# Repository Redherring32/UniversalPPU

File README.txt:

Release date: August 11, 2014

Contained within is all the information you should need to build and program your very own Universal PPU.

Here are the brief programming instructions:
1. Load the microcontroller with the firmware.  You will need a Pickit or equivalent programmer to do this.
2. Load PaletteMaker.  Write out a palette file.
3. Connect the Universal PPU to your computer via a USB cable.
4. Load UniversalPpuConfig.  Connect to your Universal PPU.
5. Under the FPGA tab, load universalppu.bin (NOT universalppu.bit).  Write the FPGA.
6. Under the Palette tab, load your palette file.  Write it.

And that's it!  Good luck!

Please note that there is no warranty nor any support offered for the contents of this archive.  
Assembling your own Universal PPU is strictly at your own risk.

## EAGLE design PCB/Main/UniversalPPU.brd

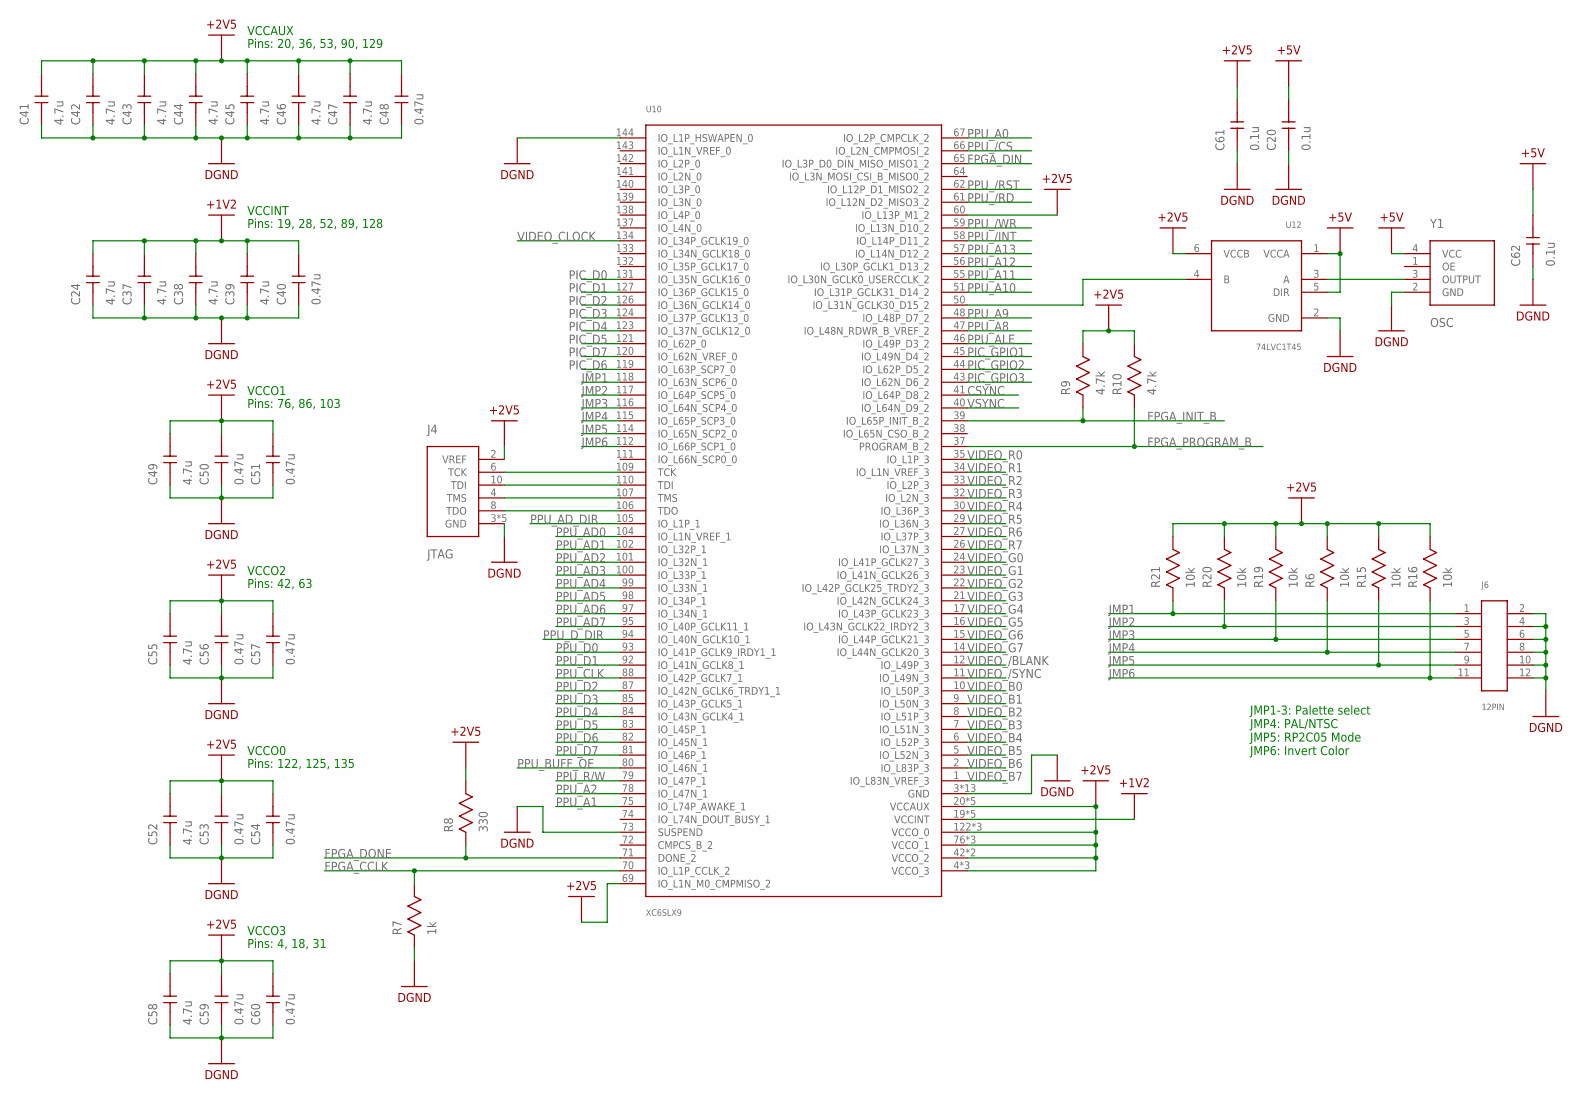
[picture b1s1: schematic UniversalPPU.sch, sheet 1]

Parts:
C20, C61, C62: 0.1u; TDK_C0816
C24, C37, C38, C39, C41, C42, C43, C44, C45, C46, C47, C49, C52, C55, C58: 4.7u; TDK_C0816
C40, C48, C50, C51, C53, C54, C56, C57, C59, C60: 0.47u; TDK_C0816
J4: JTAG; 14PIN_2MM
J6: 12PIN
R6, R15, R16, R19, R20, R21: 10k; 0603
R7: 1k; 0603
R8: 330; 0603
R9, R10: 4.7k; 0603
U10: XC6SLX9; TQG144
U12: 74LVC1T45; R-PDSO-G6
Y1: OSC

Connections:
+1V2: C24.2, C37.2, C38.2, C39.2, C40.2, U10.19 (VCCINT), U10.28 (VCCINT), U10.52 (VCCINT), U10.89 (VCCINT), U10.128 (VCCINT); also elsewhere on the board
+2V5: C41.2, C42.2, C43.2, C44.2, C45.2, C46.2, C47.2, C48.2, C49.2, C50.2, C51.2, C52.2, C53.2, C54.2, C55.2, C56.2, C57.2, C58.2, C59.2, C60.2, C61.2, J4.2 (VREF), R6.P$2, R8.P$2, R9.P$2, R10.P$2, R15.P$2, R16.P$2, R19.P$2, R20.P$2, R21.P$2, U10.4 (VCCO_3), U10.18 (VCCO_3), U10.20 (VCCAUX), U10.31 (VCCO_3), U10.36 (VCCAUX), U10.42 (VCCO_2), U10.53 (VCCAUX), U10.60 (IO_L13P_M1_2), U10.63 (VCCO_2), U10.69 (IO_L1N_M0_CMPMISO_2), U10.76 (VCCO_1), U10.86 (VCCO_1), U10.90 (VCCAUX), U10.103 (VCCO_1), U10.122 (VCCO_0), U10.125 (VCCO_0), U10.129 (VCCAUX), U10.135 (VCCO_0), U12.6 (VCCB); also elsewhere on the board
+5V: C20.2, C62.2, U12.1 (VCCA), U12.5 (DIR), Y1.4 (VCC); also elsewhere on the board
CSYNC: U10.41 (IO_L64P_D8_2); also elsewhere on the board
DGND: C20.1, C24.1, C37.1, C38.1, C39.1, C40.1, C41.1, C42.1, C43.1, C44.1, C45.1, C46.1, C47.1, C48.1, C49.1, C50.1, C51.1, C52.1, C53.1, C54.1, C55.1, C56.1, C57.1, C58.1, C59.1, C60.1, C61.1, C62.1, J4.3 (GND), J4.5 (GND), J4.7 (GND), J4.9 (GND), J4.11 (GND), J6.2, J6.4, J6.6, J6.8, J6.10, J6.12, R7.P$1, U10.3 (GND), U10.13 (GND), U10.25 (GND), U10.49 (GND), U10.54 (GND), U10.68 (GND), U10.73 (SUSPEND), U10.77 (GND), U10.91 (GND), U10.96 (GND), U10.108 (GND), U10.113 (GND), U10.130 (GND), U10.136 (GND), U10.144 (IO_L1P_HSWAPEN_0), U12.2 (GND), Y1.2 (GND); also elsewhere on the board
FPGA_CCLK: R7.P$2, U10.70 (IO_L1P_CCLK_2); also elsewhere on the board
FPGA_DIN: U10.65 (IO_L3P_D0_DIN_MISO_MISO1_2); also elsewhere on the board
FPGA_DONE: R8.P$1, U10.71 (DONE_2); also elsewhere on the board
FPGA_INIT_B: R9.P$1, U10.39 (IO_L65P_INIT_B_2); also elsewhere on the board
FPGA_PROGRAM_B: R10.P$1, U10.37 (PROGRAM_B_2); also elsewhere on the board
JMP1: J6.1, R21.P$1, U10.118 (IO_L63N_SCP6_0)
JMP2: J6.3, R20.P$1, U10.117 (IO_L64P_SCP5_0)
JMP3: J6.5, R19.P$1, U10.116 (IO_L64N_SCP4_0)
JMP4: J6.7, R6.P$1, U10.115 (IO_L65P_SCP3_0)
JMP5: J6.9, R15.P$1, U10.114 (IO_L65N_SCP2_0)
JMP6: J6.11, R16.P$1, U10.112 (IO_L66P_SCP1_0)
unnamed: U10.50 (IO_L31N_GCLK30_D15_2), U12.4 (B)
unnamed: U12.3 (A), Y1.3 (OUTPUT)
PIC_D0: U10.131 (IO_L35N_GCLK16_0); also elsewhere on the board
PIC_D1: U10.127 (IO_L36P_GCLK15_0); also elsewhere on the board
PIC_D2: U10.126 (IO_L36N_GCLK14_0); also elsewhere on the board
PIC_D3: U10.124 (IO_L37P_GCLK13_0); also elsewhere on the board
PIC_D4: U10.123 (IO_L37N_GCLK12_0); also elsewhere on the board
PIC_D5: U10.121 (IO_L62P_0); also elsewhere on the board
PIC_D6: U10.119 (IO_L63P_SCP7_0); also elsewhere on the board
PIC_D7: U10.120 (IO_L62N_VREF_0); also elsewhere on the board
PIC_GPIO1: U10.45 (IO_L49N_D4_2); also elsewhere on the board
PIC_GPIO2: U10.44 (IO_L62P_D5_2); also elsewhere on the board
PIC_GPIO3: U10.43 (IO_L62N_D6_2); also elsewhere on the board
PPU_/CS: U10.66 (IO_L2N_CMPMOSI_2); also elsewhere on the board
PPU_/INT: U10.58 (IO_L14P_D11_2); also elsewhere on the board
PPU_/RD: U10.61 (IO_L12N_D2_MISO3_2); also elsewhere on the board
PPU_/RST: U10.62 (IO_L12P_D1_MISO2_2); also elsewhere on the board
PPU_/WR: U10.59 (IO_L13N_D10_2); also elsewhere on the board
PPU_A0: U10.67 (IO_L2P_CMPCLK_2); also elsewhere on the board
PPU_A1: U10.75 (IO_L74P_AWAKE_1); also elsewhere on the board
PPU_A2: U10.78 (IO_L47N_1); also elsewhere on the board
PPU_A8: U10.47 (IO_L48N_RDWR_B_VREF_2); also elsewhere on the board
PPU_A9: U10.48 (IO_L48P_D7_2); also elsewhere on the board
PPU_A10: U10.51 (IO_L31P_GCLK31_D14_2); also elsewhere on the board
PPU_A11: U10.55 (IO_L30N_GCLK0_USERCCLK_2); also elsewhere on the board
PPU_A12: U10.56 (IO_L30P_GCLK1_D13_2); also elsewhere on the board
PPU_A13: U10.57 (IO_L14N_D12_2); also elsewhere on the board
PPU_AD0: U10.104 (IO_L1N_VREF_1); also elsewhere on the board
PPU_AD1: U10.102 (IO_L32P_1); also elsewhere on the board
PPU_AD2: U10.101 (IO_L32N_1); also elsewhere on the board
PPU_AD3: U10.100 (IO_L33P_1); also elsewhere on the board
PPU_AD4: U10.99 (IO_L33N_1); also elsewhere on the board
PPU_AD5: U10.98 (IO_L34P_1); also elsewhere on the board
PPU_AD6: U10.97 (IO_L34N_1); also elsewhere on the board
PPU_AD7: U10.95 (IO_L40P_GCLK11_1); also elsewhere on the board
PPU_AD_DIR: U10.105 (IO_L1P_1); also elsewhere on the board
PPU_ALE: U10.46 (IO_L49P_D3_2); also elsewhere on the board
PPU_BUFF_OE: U10.80 (IO_L46N_1); also elsewhere on the board
PPU_CLK: U10.88 (IO_L42P_GCLK7_1); also elsewhere on the board
PPU_D0: U10.93 (IO_L41P_GCLK9_IRDY1_1); also elsewhere on the board
PPU_D1: U10.92 (IO_L41N_GCLK8_1); also elsewhere on the board
PPU_D2: U10.87 (IO_L42N_GCLK6_TRDY1_1); also elsewhere on the board
PPU_D3: U10.85 (IO_L43P_GCLK5_1); also elsewhere on the board
PPU_D4: U10.84 (IO_L43N_GCLK4_1); also elsewhere on the board
PPU_D5: U10.83 (IO_L45P_1); also elsewhere on the board
PPU_D6: U10.82 (IO_L45N_1); also elsewhere on the board
PPU_D7: U10.81 (IO_L46P_1); also elsewhere on the board
PPU_D_DIR: U10.94 (IO_L40N_GCLK10_1); also elsewhere on the board
PPU_R/W: U10.79 (IO_L47P_1); also elsewhere on the board
TCK: J4.6 (TCK), U10.109 (TCK)
TDI: J4.10 (TDI), U10.110 (TDI)
TDO: J4.8 (TDO), U10.106 (TDO)
TMS: J4.4 (TMS), U10.107 (TMS)
VIDEO_/BLANK: U10.12 (IO_L49P_3); also elsewhere on the board
VIDEO_/SYNC: U10.11 (IO_L49N_3); also elsewhere on the board
VIDEO_B0: U10.10 (IO_L50P_3); also elsewhere on the board
VIDEO_B1: U10.9 (IO_L50N_3); also elsewhere on the board
VIDEO_B2: U10.8 (IO_L51P_3); also elsewhere on the board
VIDEO_B3: U10.7 (IO_L51N_3); also elsewhere on the board
VIDEO_B4: U10.6 (IO_L52P_3); also elsewhere on the board
VIDEO_B5: U10.5 (IO_L52N_3); also elsewhere on the board
VIDEO_B6: U10.2 (IO_L83P_3); also elsewhere on the board
VIDEO_B7: U10.1 (IO_L83N_VREF_3); also elsewhere on the board
VIDEO_CLOCK: U10.134 (IO_L34P_GCLK19_0); also elsewhere on the board
VIDEO_G0: U10.24 (IO_L41P_GCLK27_3); also elsewhere on the board
VIDEO_G1: U10.23 (IO_L41N_GCLK26_3); also elsewhere on the board
VIDEO_G2: U10.22 (IO_L42P_GCLK25_TRDY2_3); also elsewhere on the board
VIDEO_G3: U10.21 (IO_L42N_GCLK24_3); also elsewhere on the board
VIDEO_G4: U10.17 (IO_L43P_GCLK23_3); also elsewhere on the board
VIDEO_G5: U10.16 (IO_L43N_GCLK22_IRDY2_3); also elsewhere on the board
VIDEO_G6: U10.15 (IO_L44P_GCLK21_3); also elsewhere on the board
VIDEO_G7: U10.14 (IO_L44N_GCLK20_3); also elsewhere on the board
VIDEO_R0: U10.35 (IO_L1P_3); also elsewhere on the board
VIDEO_R1: U10.34 (IO_L1N_VREF_3); also elsewhere on the board
VIDEO_R2: U10.33 (IO_L2P_3); also elsewhere on the board
VIDEO_R3: U10.32 (IO_L2N_3); also elsewhere on the board
VIDEO_R4: U10.30 (IO_L36P_3); also elsewhere on the board
VIDEO_R5: U10.29 (IO_L36N_3); also elsewhere on the board
VIDEO_R6: U10.27 (IO_L37P_3); also elsewhere on the board
VIDEO_R7: U10.26 (IO_L37N_3); also elsewhere on the board
VSYNC: U10.40 (IO_L64N_D9_2); also elsewhere on the board

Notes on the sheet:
VCCINT
VCCAUX
VCCO1
VCCO2
VCCO0
VCCO3
JMP1-3: Palette select JMP4: PAL/NTSC JMP5: RP2C05 Mode JMP6: Invert Color
Pins: 20, 36, 53, 90, 129
Pins: 19, 28, 52, 89, 128
Pins: 76, 86, 103
Pins: 42, 63
Pins: 122, 125, 135
Pins: 4, 18, 31

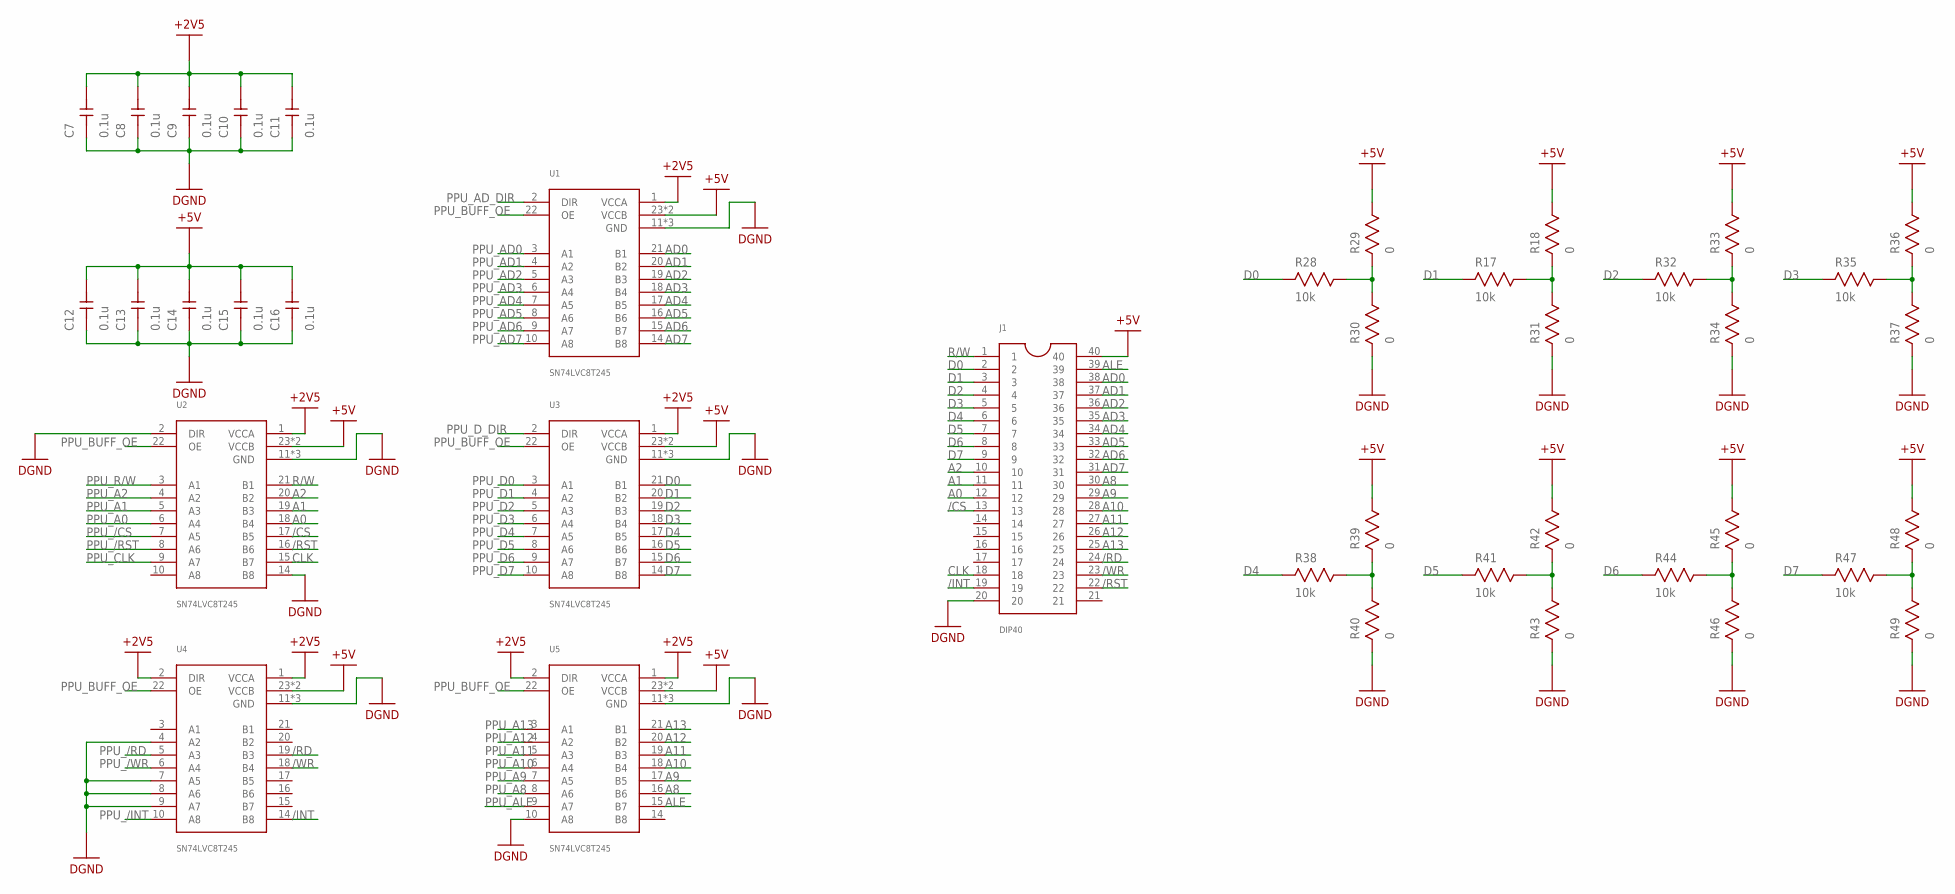
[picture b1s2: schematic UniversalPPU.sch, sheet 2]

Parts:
C7, C8, C9, C10, C11, C12, C13, C14, C15, C16: 0.1u; TDK_C0816
J1: DIP40
R17, R28, R32, R35, R38, R41, R44, R47: 10k; 0603
R18, R29, R30, R31, R33, R34, R36, R37, R39, R40, R42, R43, R45, R46, R48, R49: 0; 0603
U1, U2, U3, U4, U5: SN74LVC8T245; TSSOP24

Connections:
+2V5: C7.2, C8.2, C9.2, C10.2, C11.2, U1.1 (VCCA), U2.1 (VCCA), U3.1 (VCCA), U4.1 (VCCA), U4.2 (DIR), U5.1 (VCCA), U5.2 (DIR); also elsewhere on the board
+5V: C12.2, C13.2, C14.2, C15.2, C16.2, J1.40, R18.P$2, R29.P$2, R33.P$2, R36.P$2, R39.P$2, R42.P$2, R45.P$2, R48.P$2, U1.23 (VCCB), U1.24 (VCCB), U2.23 (VCCB), U2.24 (VCCB), U3.23 (VCCB), U3.24 (VCCB), U4.23 (VCCB), U4.24 (VCCB), U5.23 (VCCB), U5.24 (VCCB); also elsewhere on the board
/CS: J1.13, U2.17 (B5)
/INT: J1.19, U4.14 (B8)
/RD: J1.24, U4.19 (B3)
/RST: J1.22, U2.16 (B6)
/WR: J1.23, U4.18 (B4)
A0: J1.12, U2.18 (B4)
A1: J1.11, U2.19 (B3)
A2: J1.10, U2.20 (B2)
A8: J1.30, U5.16 (B6)
A9: J1.29, U5.17 (B5)
A10: J1.28, U5.18 (B4)
A11: J1.27, U5.19 (B3)
A12: J1.26, U5.20 (B2)
A13: J1.25, U5.21 (B1)
AD0: J1.38, U1.21 (B1)
AD1: J1.37, U1.20 (B2)
AD2: J1.36, U1.19 (B3)
AD3: J1.35, U1.18 (B4)
AD4: J1.34, U1.17 (B5)
AD5: J1.33, U1.16 (B6)
AD6: J1.32, U1.15 (B7)
AD7: J1.31, U1.14 (B8)
ALE: J1.39, U5.15 (B7)
CLK: J1.18, U2.15 (B7)
D0: J1.2, R28.P$1, U3.21 (B1)
D1: J1.3, R17.P$1, U3.20 (B2)
D2: J1.4, R32.P$1, U3.19 (B3)
D3: J1.5, R35.P$1, U3.18 (B4)
D4: J1.6, R38.P$1, U3.17 (B5)
D5: J1.7, R41.P$1, U3.16 (B6)
D6: J1.8, R44.P$1, U3.15 (B7)
D7: J1.9, R47.P$1, U3.14 (B8)
DGND: C7.1, C8.1, C9.1, C10.1, C11.1, C12.1, C13.1, C14.1, C15.1, C16.1, J1.20, R30.P$1, R31.P$1, R34.P$1, R37.P$1, R40.P$1, R43.P$1, R46.P$1, R49.P$1, U1.11 (GND), U1.12 (GND), U1.13 (GND), U2.2 (DIR), U2.11 (GND), U2.12 (GND), U2.13 (GND), U2.14 (B8), U3.11 (GND), U3.12 (GND), U3.13 (GND), U4.4 (A2), U4.7 (A5), U4.8 (A6), U4.9 (A7), U4.11 (GND), U4.12 (GND), U4.13 (GND), U5.10 (A8), U5.11 (GND), U5.12 (GND), U5.13 (GND); also elsewhere on the board
unnamed: R28.P$2, R29.P$1, R30.P$2
unnamed: R17.P$2, R18.P$1, R31.P$2
unnamed: R32.P$2, R33.P$1, R34.P$2
unnamed: R35.P$2, R36.P$1, R37.P$2
unnamed: R38.P$2, R39.P$1, R40.P$2
unnamed: R41.P$2, R42.P$1, R43.P$2
unnamed: R44.P$2, R45.P$1, R46.P$2
unnamed: R47.P$2, R48.P$1, R49.P$2
PPU_/CS: U2.7 (A5); also elsewhere on the board
PPU_/INT: U4.10 (A8); also elsewhere on the board
PPU_/RD: U4.5 (A3); also elsewhere on the board
PPU_/RST: U2.8 (A6); also elsewhere on the board
PPU_/WR: U4.6 (A4); also elsewhere on the board
PPU_A0: U2.6 (A4); also elsewhere on the board
PPU_A1: U2.5 (A3); also elsewhere on the board
PPU_A2: U2.4 (A2); also elsewhere on the board
PPU_A8: U5.8 (A6); also elsewhere on the board
PPU_A9: U5.7 (A5); also elsewhere on the board
PPU_A10: U5.6 (A4); also elsewhere on the board
PPU_A11: U5.5 (A3); also elsewhere on the board
PPU_A12: U5.4 (A2); also elsewhere on the board
PPU_A13: U5.3 (A1); also elsewhere on the board
PPU_AD0: U1.3 (A1); also elsewhere on the board
PPU_AD1: U1.4 (A2); also elsewhere on the board
PPU_AD2: U1.5 (A3); also elsewhere on the board
PPU_AD3: U1.6 (A4); also elsewhere on the board
PPU_AD4: U1.7 (A5); also elsewhere on the board
PPU_AD5: U1.8 (A6); also elsewhere on the board
PPU_AD6: U1.9 (A7); also elsewhere on the board
PPU_AD7: U1.10 (A8); also elsewhere on the board
PPU_AD_DIR: U1.2 (DIR); also elsewhere on the board
PPU_ALE: U5.9 (A7); also elsewhere on the board
PPU_BUFF_OE: U1.22 (OE), U2.22 (OE), U3.22 (OE), U4.22 (OE), U5.22 (OE); also elsewhere on the board
PPU_CLK: U2.9 (A7); also elsewhere on the board
PPU_D0: U3.3 (A1); also elsewhere on the board
PPU_D1: U3.4 (A2); also elsewhere on the board
PPU_D2: U3.5 (A3); also elsewhere on the board
PPU_D3: U3.6 (A4); also elsewhere on the board
PPU_D4: U3.7 (A5); also elsewhere on the board
PPU_D5: U3.8 (A6); also elsewhere on the board
PPU_D6: U3.9 (A7); also elsewhere on the board
PPU_D7: U3.10 (A8); also elsewhere on the board
PPU_D_DIR: U3.2 (DIR); also elsewhere on the board
PPU_R/W: U2.3 (A1); also elsewhere on the board
R/W: J1.1, U2.21 (B1)

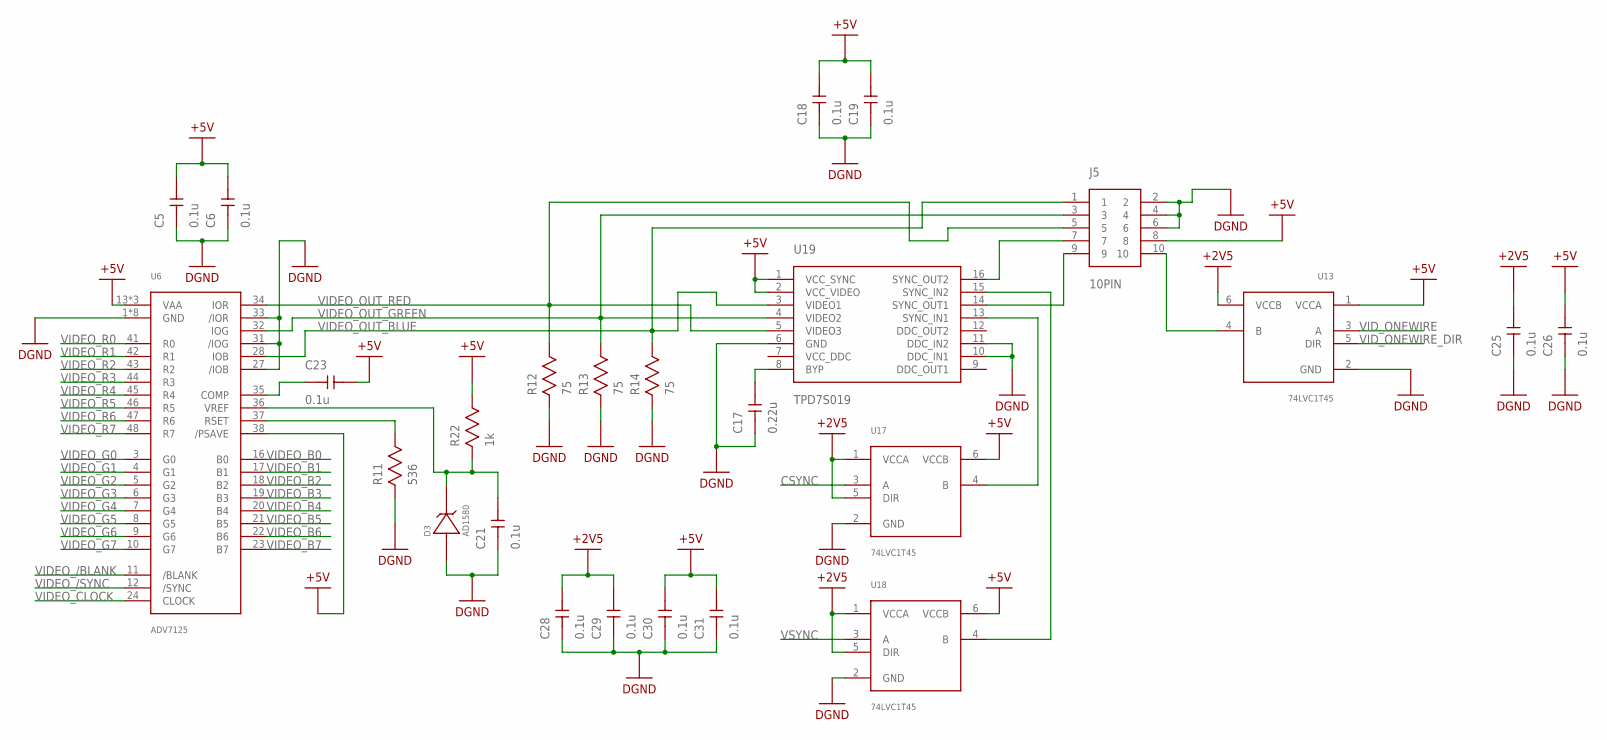
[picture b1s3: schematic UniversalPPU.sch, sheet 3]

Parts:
C5, C6, C18, C19, C21, C23, C25, C26, C28, C29, C30, C31: 0.1u; TDK_C0816
C17: 0.22u; TDK_C0816
D3: AD1580; SOT-23-3
J5: 10PIN
R11: 536; 0603
R12, R13, R14: 75; 0603
R22: 1k; 0603
U6: ADV7125; LQFP-48
U13, U17, U18: 74LVC1T45; R-PDSO-G6
U19: TPD7S019; R-PDSO-G16

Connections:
+2V5: C25.2, C28.2, C29.2, U13.6 (VCCB), U17.1 (VCCA), U17.5 (DIR), U18.1 (VCCA), U18.5 (DIR); also elsewhere on the board
+5V: C5.2, C6.2, C18.2, C19.2, C23.2, C26.2, C30.2, C31.2, J5.8, R22.P$2, U6.13 (VAA), U6.29 (VAA), U6.30 (VAA), U6.38 (/PSAVE), U13.1 (VCCA), U17.6 (VCCB), U18.6 (VCCB), U19.1 (VCC_SYNC), U19.2 (VCC_VIDEO); also elsewhere on the board
CSYNC: U17.3 (A); also elsewhere on the board
DGND: C5.1, C6.1, C17.1, C18.1, C19.1, C21.1, C25.1, C26.1, C28.1, C29.1, C30.1, C31.1, D3.2 (V-), J5.2, J5.4, J5.6, R11.P$1, R12.P$1, R13.P$1, R14.P$1, U6.1 (GND), U6.2 (GND), U6.14 (GND), U6.15 (GND), U6.25 (GND), U6.26 (GND), U6.27 (/IOB), U6.31 (/IOG), U6.33 (/IOR), U6.39 (GND), U6.40 (GND), U13.2 (GND), U17.2 (GND), U18.2 (GND), U19.6 (GND), U19.10 (DDC_IN1), U19.11 (DDC_IN2); also elsewhere on the board
unnamed: C23.1, U6.35 (COMP)
unnamed: U17.4 (B), U19.13 (SYNC_IN1)
unnamed: C21.2, D3.1 (V+), R22.P$1, U6.36 (VREF)
unnamed: R11.P$2, U6.37 (RSET)
unnamed: J5.10, U13.4 (B)
unnamed: C17.2, U19.8 (BYP)
unnamed: U18.4 (B), U19.15 (SYNC_IN2)
unnamed: J5.7, U19.16 (SYNC_OUT2)
unnamed: J5.9, U19.14 (SYNC_OUT1)
VIDEO_/BLANK: U6.11 (/BLANK); also elsewhere on the board
VIDEO_/SYNC: U6.12 (/SYNC); also elsewhere on the board
VIDEO_B0: U6.16 (B0); also elsewhere on the board
VIDEO_B1: U6.17 (B1); also elsewhere on the board
VIDEO_B2: U6.18 (B2); also elsewhere on the board
VIDEO_B3: U6.19 (B3); also elsewhere on the board
VIDEO_B4: U6.20 (B4); also elsewhere on the board
VIDEO_B5: U6.21 (B5); also elsewhere on the board
VIDEO_B6: U6.22 (B6); also elsewhere on the board
VIDEO_B7: U6.23 (B7); also elsewhere on the board
VIDEO_CLOCK: U6.24 (CLOCK); also elsewhere on the board
VIDEO_G0: U6.3 (G0); also elsewhere on the board
VIDEO_G1: U6.4 (G1); also elsewhere on the board
VIDEO_G2: U6.5 (G2); also elsewhere on the board
VIDEO_G3: U6.6 (G3); also elsewhere on the board
VIDEO_G4: U6.7 (G4); also elsewhere on the board
VIDEO_G5: U6.8 (G5); also elsewhere on the board
VIDEO_G6: U6.9 (G6); also elsewhere on the board
VIDEO_G7: U6.10 (G7); also elsewhere on the board
VIDEO_OUT_BLUE: J5.1, R14.P$2, U6.28 (IOB), U19.3 (VIDEO1)
VIDEO_OUT_GREEN: J5.3, R13.P$2, U6.32 (IOG), U19.4 (VIDEO2)
VIDEO_OUT_RED: J5.5, R12.P$2, U6.34 (IOR), U19.5 (VIDEO3)
VIDEO_R0: U6.41 (R0); also elsewhere on the board
VIDEO_R1: U6.42 (R1); also elsewhere on the board
VIDEO_R2: U6.43 (R2); also elsewhere on the board
VIDEO_R3: U6.44 (R3); also elsewhere on the board
VIDEO_R4: U6.45 (R4); also elsewhere on the board
VIDEO_R5: U6.46 (R5); also elsewhere on the board
VIDEO_R6: U6.47 (R6); also elsewhere on the board
VIDEO_R7: U6.48 (R7); also elsewhere on the board
VID_ONEWIRE: U13.3 (A); also elsewhere on the board
VID_ONEWIRE_DIR: U13.5 (DIR); also elsewhere on the board
VSYNC: U18.3 (A); also elsewhere on the board

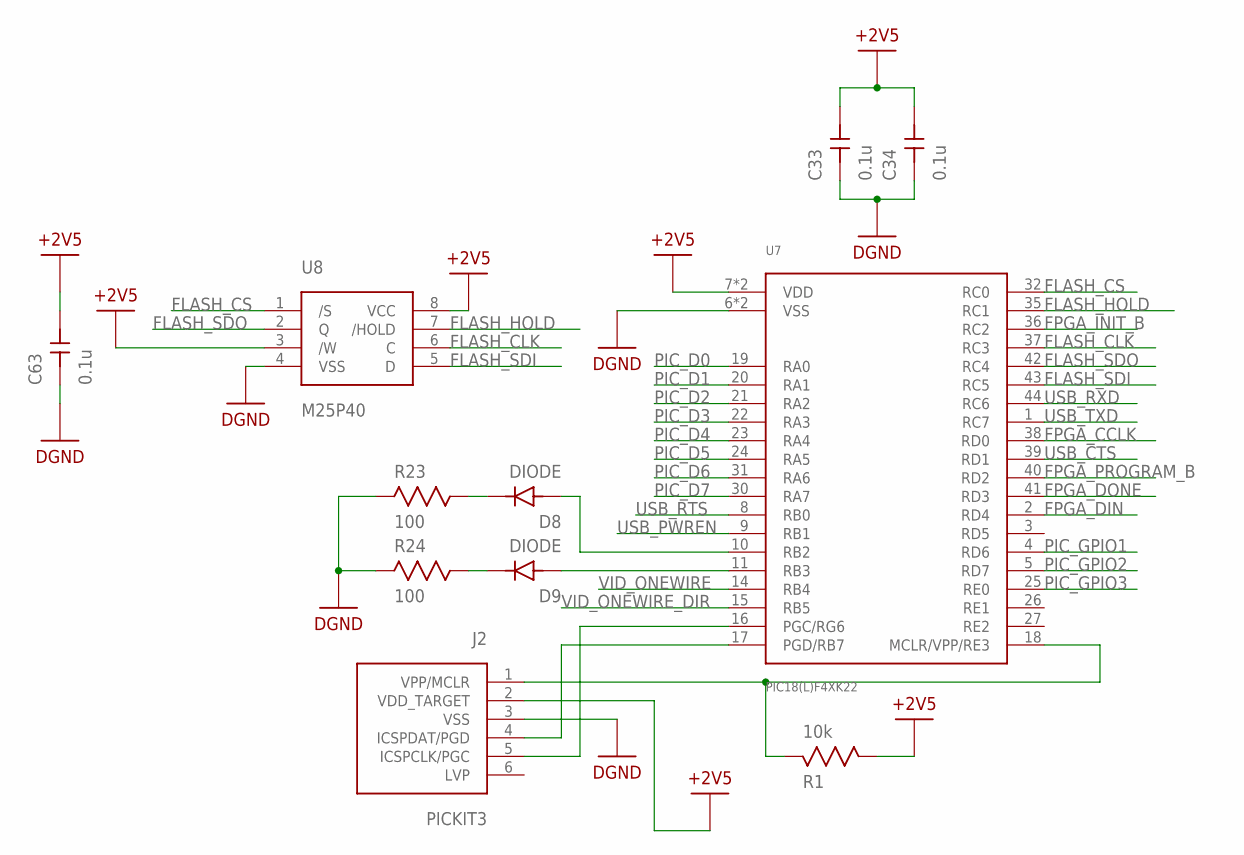
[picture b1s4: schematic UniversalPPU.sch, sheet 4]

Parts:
C33, C34, C63: 0.1u; TDK_C0816
D8, D9: DIODE; LED_0603
J2: PICKIT3; 6SIP
R1: 10k; 0603
R23, R24: 100; 0603
U7: PIC18(L)F4XK22; TQFP44
U8: M25P40; 8PIN

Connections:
+2V5: C33.2, C34.2, C63.2, J2.2 (VDD_TARGET), R1.P$2, U7.7 (VDD), U7.28 (VDD), U8.3 (/W), U8.8 (VCC); also elsewhere on the board
DGND: C33.1, C34.1, C63.1, J2.3 (VSS), R23.P$1, R24.P$1, U7.6 (VSS), U7.29 (VSS), U8.4 (VSS); also elsewhere on the board
FLASH_CLK: U7.37 (RC3), U8.6 (C)
FLASH_CS: U7.32 (RC0), U8.1 (/S)
FLASH_HOLD: U7.35 (RC1), U8.7 (/HOLD)
FLASH_SDI: U7.43 (RC5), U8.5 (D)
FLASH_SDO: U7.42 (RC4), U8.2 (Q)
FPGA_CCLK: U7.38 (RD0); also elsewhere on the board
FPGA_DIN: U7.2 (RD4); also elsewhere on the board
FPGA_DONE: U7.41 (RD3); also elsewhere on the board
FPGA_INIT_B: U7.36 (RC2); also elsewhere on the board
FPGA_PROGRAM_B: U7.40 (RD2); also elsewhere on the board
unnamed: J2.4 (ICSPDAT/PGD), U7.17 (PGD/RB7)
unnamed: J2.1 (VPP/MCLR), R1.P$1, U7.18 (MCLR/VPP/RE3)
unnamed: J2.5 (ICSPCLK/PGC), U7.16 (PGC/RG6)
unnamed: D8.A, U7.10 (RB2)
unnamed: D9.A, U7.11 (RB3)
unnamed: D8.C, R23.P$2
unnamed: D9.C, R24.P$2
PIC_D0: U7.19 (RA0); also elsewhere on the board
PIC_D1: U7.20 (RA1); also elsewhere on the board
PIC_D2: U7.21 (RA2); also elsewhere on the board
PIC_D3: U7.22 (RA3); also elsewhere on the board
PIC_D4: U7.23 (RA4); also elsewhere on the board
PIC_D5: U7.24 (RA5); also elsewhere on the board
PIC_D6: U7.31 (RA6); also elsewhere on the board
PIC_D7: U7.30 (RA7); also elsewhere on the board
PIC_GPIO1: U7.4 (RD6); also elsewhere on the board
PIC_GPIO2: U7.5 (RD7); also elsewhere on the board
PIC_GPIO3: U7.25 (RE0); also elsewhere on the board
USB_CTS: U7.39 (RD1); also elsewhere on the board
USB_PWREN: U7.9 (RB1); also elsewhere on the board
USB_RTS: U7.8 (RB0); also elsewhere on the board
USB_RXD: U7.44 (RC6); also elsewhere on the board
USB_TXD: U7.1 (RC7); also elsewhere on the board
VID_ONEWIRE: U7.14 (RB4); also elsewhere on the board
VID_ONEWIRE_DIR: U7.15 (RB5); also elsewhere on the board

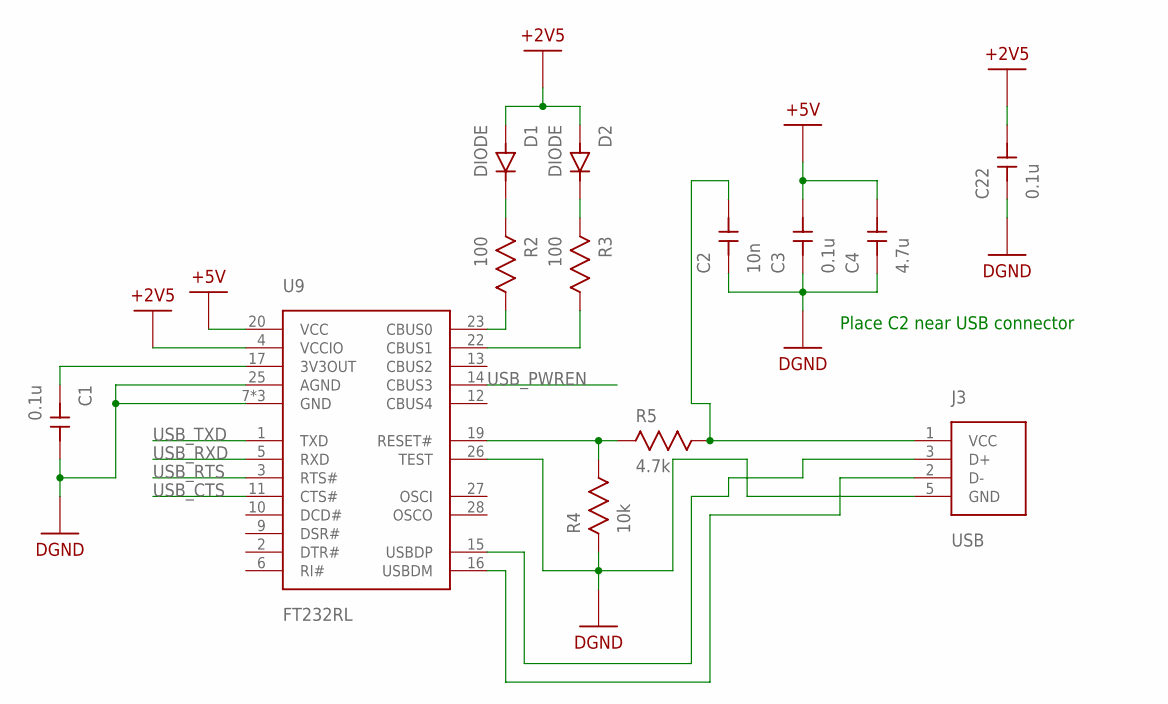
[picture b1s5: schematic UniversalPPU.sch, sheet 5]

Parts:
C1, C3, C22: 0.1u; TDK_C0816
C2: 10n; TDK_C0816
C4: 4.7u; TDK_C0816
D1, D2: DIODE; LED_0603
J3: USB
R2, R3: 100; 0603
R4: 10k; 0603
R5: 4.7k; 0603
U9: FT232RL; SSOP-28

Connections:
+2V5: C22.2, D1.A, D2.A, U9.4 (VCCIO); also elsewhere on the board
+5V: C3.2, C4.2, U9.20 (VCC); also elsewhere on the board
DGND: C1.2, C2.1, C3.1, C4.1, C22.1, J3.5 (GND), R4.P$1, U9.7 (GND), U9.18 (GND), U9.21 (GND), U9.25 (AGND), U9.26 (TEST); also elsewhere on the board
unnamed: R4.P$2, R5.P$1, U9.19 (RESET#)
unnamed: J3.3 (D+), U9.15 (USBDP)
unnamed: C1.1, U9.17 (3V3OUT)
unnamed: R2.P$2, U9.23 (CBUS0)
unnamed: R3.P$2, U9.22 (CBUS1)
unnamed: J3.2 (D-), U9.16 (USBDM)
unnamed: D1.C, R2.P$1
unnamed: D2.C, R3.P$1
unnamed: C2.2, J3.1 (VCC), R5.P$2
USB_CTS: U9.11 (CTS#); also elsewhere on the board
USB_PWREN: U9.14 (CBUS3); also elsewhere on the board
USB_RTS: U9.3 (RTS#); also elsewhere on the board
USB_RXD: U9.5 (RXD); also elsewhere on the board
USB_TXD: U9.1 (TXD); also elsewhere on the board

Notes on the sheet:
Place C2 near USB connector

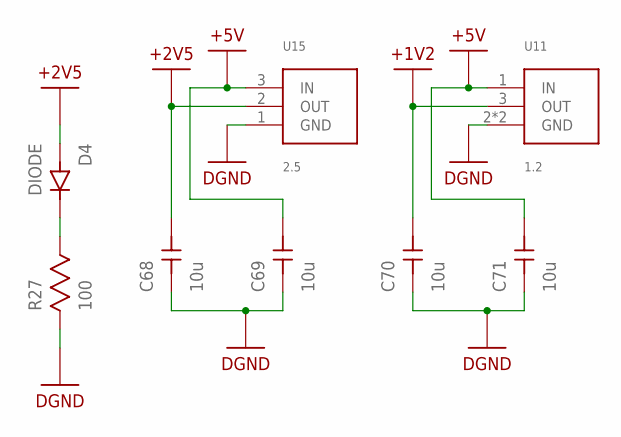
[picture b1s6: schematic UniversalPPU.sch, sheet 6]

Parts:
C68, C69, C70, C71: 10u; TDK_C1632
D4: DIODE; LED_0603
R27: 100; 0603
U11: 1.2; SOT-223
U15: 2.5; SOT-223

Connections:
+1V2: C70.2, U11.3 (OUT); also elsewhere on the board
+2V5: C68.2, D4.A, U15.2 (OUT); also elsewhere on the board
+5V: C69.2, C71.2, U11.1 (IN), U15.3 (IN); also elsewhere on the board
DGND: C68.1, C69.1, C70.1, C71.1, R27.P$1, U11.2 (GND), U11.4 (GND), U15.1 (GND); also elsewhere on the board
unnamed: D4.C, R27.P$2

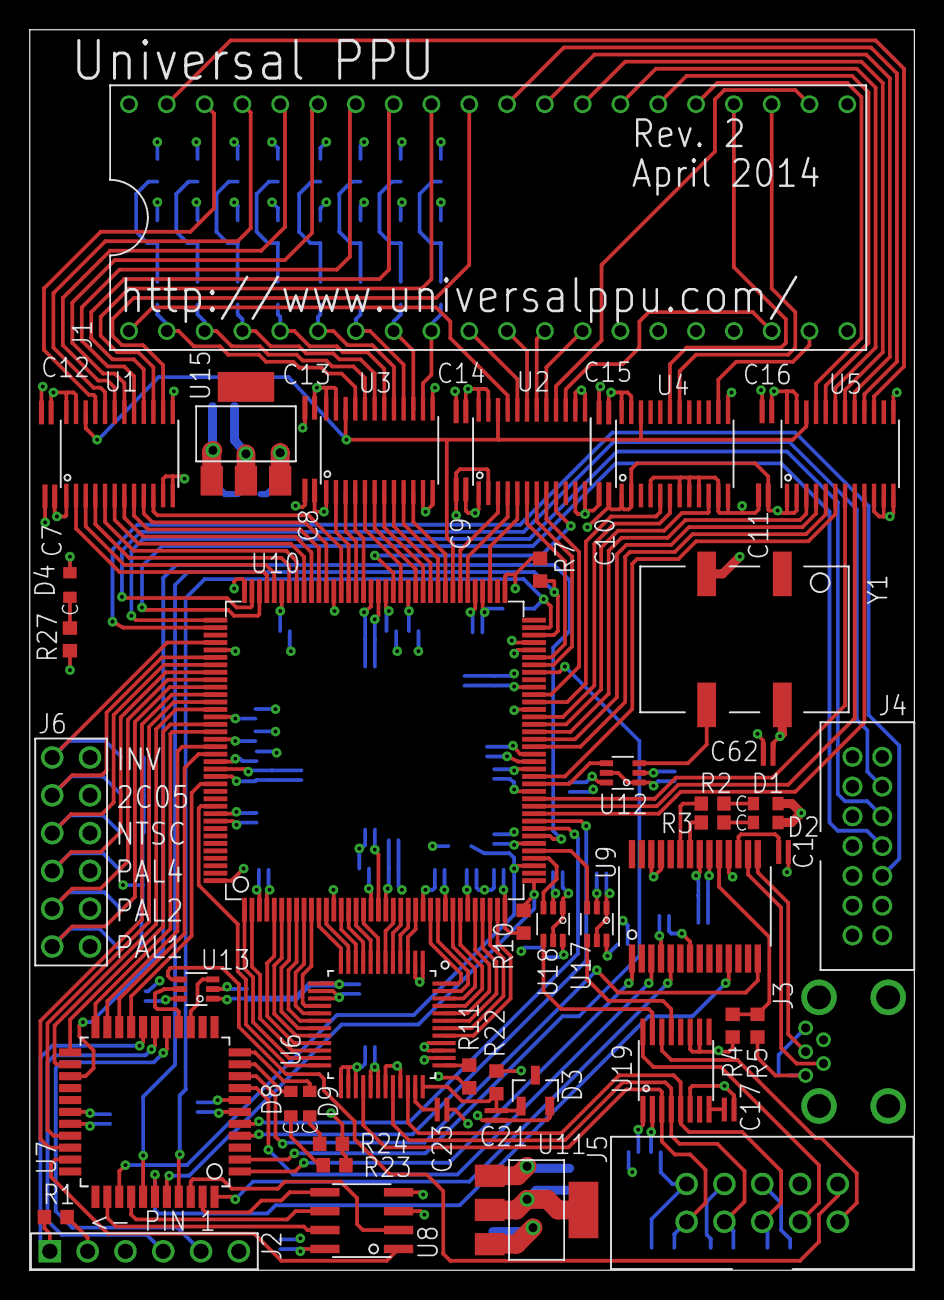
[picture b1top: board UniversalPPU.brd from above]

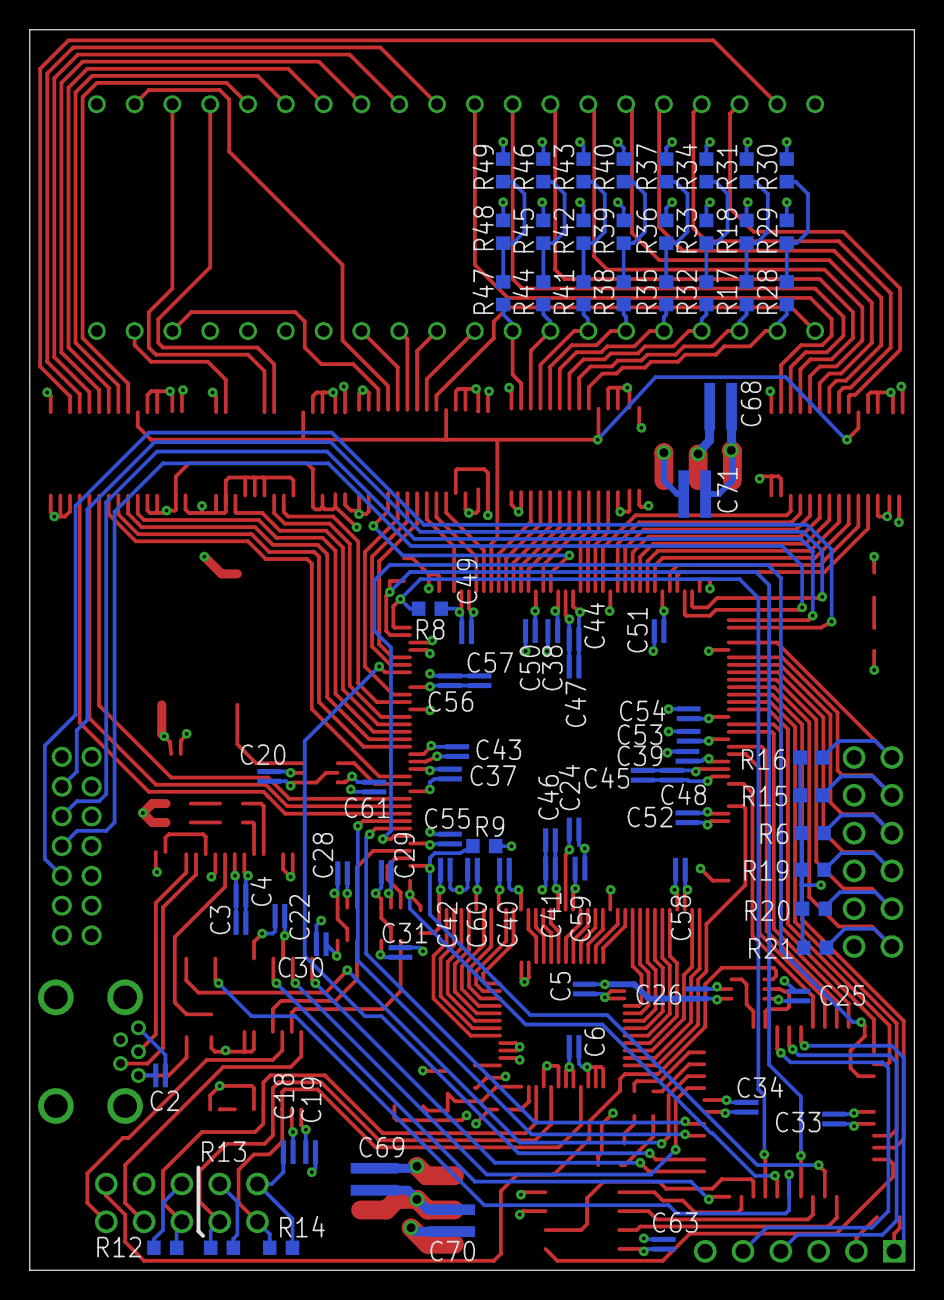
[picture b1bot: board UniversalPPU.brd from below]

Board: 4 copper layers, 59.4 x 83.3 mm, 140 parts (83 on the bottom side), 179 nets.

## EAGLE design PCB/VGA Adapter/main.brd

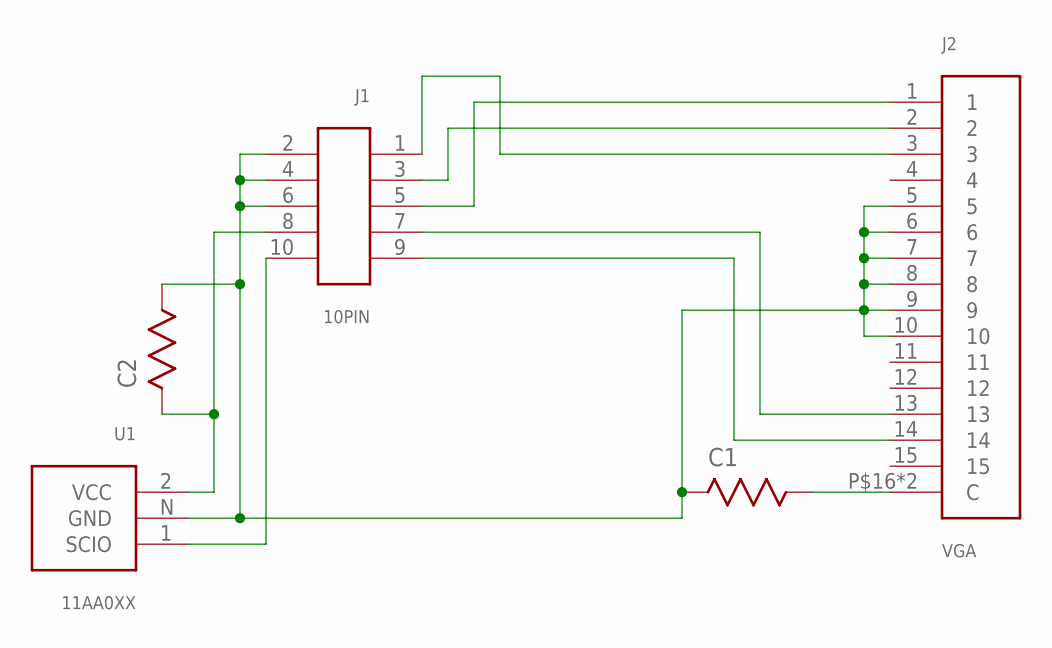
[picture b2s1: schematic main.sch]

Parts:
C1, C2: RESISTOR0603; 0603
J1: 10PIN
J2: VGA
U1: 11AA0XX; SOT-23

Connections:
unnamed: J1.5, J2.1
unnamed: J1.3, J2.2
unnamed: J1.1, J2.3
unnamed: C1.P$2, J2.P$16 (C), J2.P$17 (C)
unnamed: J1.7, J2.13
unnamed: J1.9, J2.14
unnamed: C1.P$1, C2.P$2, J1.2, J1.4, J1.6, J2.5, J2.6, J2.7, J2.8, J2.9, J2.10, U1.N (GND)
unnamed: C2.P$1, J1.8, U1.2 (VCC)
unnamed: J1.10, U1.1 (SCIO)

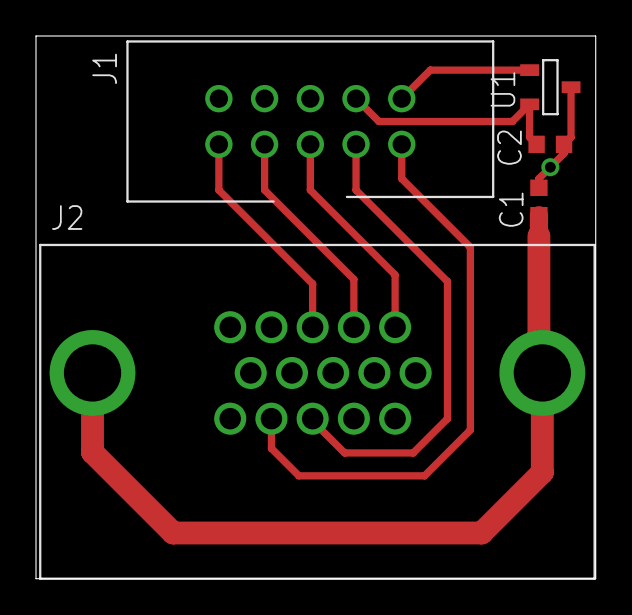
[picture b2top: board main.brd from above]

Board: 2 copper layers, 31.1 x 30.1 mm, 5 parts (0 on the bottom side), 9 nets.
